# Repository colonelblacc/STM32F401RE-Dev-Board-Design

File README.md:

# STM32F401RETx — Custom PCB Design

> A compact, 2-layer custom PCB based on the **STM32F401RETx** microcontroller, featuring USB-C, SWD debugging, UART, SPI, I2C and GPIO expansion — designed in KiCad and fully verified with **0 DRC errors** and **0 ERC violations**.

---

## Board Preview

---

## Project Phases

This repository covers the complete design lifecycle:

| Phase   | Contents                                                                 | Status      |
|---------|--------------------------------------------------------------------------|-------------|
| Phase 1 | KiCad source files — schematic, PCB layout, project config               | ✅ Complete |
| Phase 2 | 3D renders, layer exports, BOM, DRC/ERC verification, design report      | ✅ Complete |

> **Phase 1** files (`STM32.kicad_sch`, `STM32.kicad_pcb`, `STM32.kicad_pro`) were uploaded in the first submission.
> **Phase 2** adds all supporting documentation, renders, and verification results — completing the full project.

---

## Repository Structure

```
STM32F401RE-Dev-Board-Design/
│
├── STM32.kicad_pcb                        # [Phase 1] KiCad PCB layout
├── STM32.kicad_pro                        # [Phase 1] KiCad project file
├── STM32.kicad_sch                        # [Phase 1] KiCad schematic
│
├── STM32_F401_Design_Report.pdf           # [Phase 2] Full design report
├── STM32_PDF.pdf                          # [Phase 2] Supplementary PDF
│
├── PCB Layout/
│   ├── STM32.zip                          # KiCad project archive
│   └── STM32_pcb_layer.zip                # Exported PCB layer files (Gerbers)
│
├── Render Images/
│   ├── STM32_img.png                      # 3D Render — Top View (clean)
│   ├── 3D Design.jpeg                     # 3D Render — KiCad Viewer Top
│   ├── IMAGE5.jpeg                        # 3D Render — PCB Back View
│   ├── IMAGE6.jpeg                        # 3D Render — Perspective View
│   ├── Layout Layer1.jpeg                 # F.Cu Front Copper Layer
│   ├── Layout Layer2.jpeg                 # B.Cu Back Copper Layer
│   ├── Schematic.jpeg                     # Full Schematic Diagram
│   ├── IMAGE1.jpeg                        # DRC Result — 0 Errors
│   └── IMAGE2.jpeg                        # ERC Result — 0 Violations
│
├── BOM/
│   ├── BOM.jpeg                           # Footprint Assignments View
│   └── BOM2.png                           # Bill of Materials Table
│
└── DRC ERC Results/
    ├── IMAGE1.jpeg     # DRC — 0 Violations
    └── IMAGE2.jpeg # ERC — 0 Violations
```

---

## Microcontroller

| Parameter       | Details                           |
|-----------------|-----------------------------------|
| **MCU**         | STM32F401RETx                     |
| **Package**     | LQFP-64 (10x10mm, 0.5mm pitch)    |
| **Core**        | ARM Cortex-M4 @ 84 MHz            |
| **Flash**       | 512 KB                            |
| **RAM**         | 96 KB SRAM                        |
| **EDA Tool**    | KiCad EDA 9.0.7                   |
| **PCB Layers**  | 2 (F.Cu + B.Cu)                   |

---

## Features & Connectivity

| Interface     | Connector/Ref | Description                           |
|---------------|---------------|---------------------------------------|
| **USB-C**     | J7            | USB 2.0 (USB_C_Receptacle_USB3.0_C6P)|
| **GPIO**      | J6            | 5-pin GPIO Expansion Header           |
| **SPI**       | J5            | VCC, SPI, GND Header                  |
| **UART**      | J3            | TX / RX Header                        |
| **I2C**       | J2 / J4       | SDA / SCL Header                      |
| **SWD**       | J2            | SWDIO, SWDCLK, IO, VCC, GND          |
| **RESET**     | SW1 + J4      | Tactile push button + Reset pin header|
| **Power**     | U1 (AMS1117)  | 3.3V LDO Regulator from USB 5V        |
| **Crystal**   | Y1            | 24 MHz SMD Crystal (3225-4Pin)        |
| **LED**       | D1            | Power / Status LED (0603)             |

---

## Schematic

The schematic is divided into functional blocks:

- **STM32F401** — Central MCU with all peripheral nets routed
- **Power Supply** — AMS1117-3.3 LDO with bulk and decoupling capacitors
- **USB-C Connector** — With 5.1k CC1/CC2 pull-down resistors (R7, R8)
- **Crystal** — 24 MHz with 22pF load capacitors C12, C13
- **Header Breakouts** — UART, SPI, I2C, GPIO, SWD
- **Mounting Holes** — H1–H4 (M2.5, 2.7mm diameter)

---

## PCB Layout

### Front Copper Layer — F.Cu

### Back Copper Layer — B.Cu

**PCB Statistics:**

| Parameter        | Value     |
|------------------|-----------|
| Pads             | 172       |
| Vias             | 44        |
| Track Segments   | 376       |
| Nets             | 65        |
| Unrouted         | **0**     |
| Track Width      | 0.25 mm   |

---

## Bill of Materials (BOM)

| Component              | Ref.    | Qty.   | Est. Unit Cost | Est. Total  |
|------------------------|---------|--------|----------------|-------------|
| STM32F401RETx MCU      | U2      | 1      | Rs. 350        | Rs. 350     |
| AMS1117-3.3 Regulator  | U1      | 1      | Rs. 15         | Rs. 15      |
| USB-C Connector        | J7      | 1      | Rs. 25         | Rs. 25      |
| Crystal 24 MHz         | Y1      | 1      | Rs. 10         | Rs. 10      |
| Ferrite Bead           | FB1     | 1      | Rs. 5          | Rs. 5       |
| Capacitors (0603/0805) | C1–C14  | 14     | Rs. 2          | Rs. 28      |
| Resistors (0603)       | R1–R8   | 8      | Rs. 2          | Rs. 16      |
| LED (0603)             | D1      | 1      | Rs. 3          | Rs. 3       |
| Reset Push Button      | SW1     | 1      | Rs. 5          | Rs. 5       |
| Pin Headers 2.54mm     | J2–J6   | 5 sets | Rs. 15         | Rs. 75      |
| Mounting Hardware M2.5 | H1–H4   | 4      | Rs. 3          | Rs. 12      |
| **Estimated Total**    |         |        |                | **Rs. 844** |

---

## DRC / ERC Verification

Both checks pass with **zero errors** — the design is fully clean.

### Design Rules Check (DRC) — 0 Violations

| Check              | Result |
|--------------------|--------|
| Violations         | **0**  |
| Unconnected Items  | **0**  |
| Schematic Parity   | **0**  |

### Electrical Rules Check (ERC) — 0 Violations

| Check    | Result |
|----------|--------|
| Errors   | **0**  |
| Warnings | **0**  |

---

## 3D Renders

<table align="center">
  <tr>
    <td align="center">
      <br/>
      <b>Top View — KiCad 3D Viewer</b>
    </td>
    <td align="center">
      <br/>
      <b>Bottom View</b>
    </td>
  </tr>
  <tr>
    <td align="center" colspan="2">
      <br/>
      <b>Perspective View</b>
    </td>
  </tr>
</table>

---

## KiCad Source Files (Phase 1)

The raw KiCad design files are at the root of this repository:

| File               | Description       |
|--------------------|-------------------|
| `STM32.kicad_pcb`  | PCB Layout        |
| `STM32.kicad_sch`  | Schematic         |
| `STM32.kicad_pro`  | KiCad Project     |

---

## Documents

| File                           | Description           |
|--------------------------------|-----------------------|
| `STM32_F401_Design_Report.pdf` | Full design report    |
| `STM32_PDF.pdf`                | Supplementary PDF     |
| `PCB Layout/STM32.zip`         | KiCad project archive |

---

## Tools Used

| Tool                | Version | Purpose                |
|---------------------|---------|------------------------|
| **KiCad EDA**       | 9.0.7   | Schematic + PCB Design |
| **KiCad 3D Viewer** | 9.0.7   | 3D Visualization       |

---

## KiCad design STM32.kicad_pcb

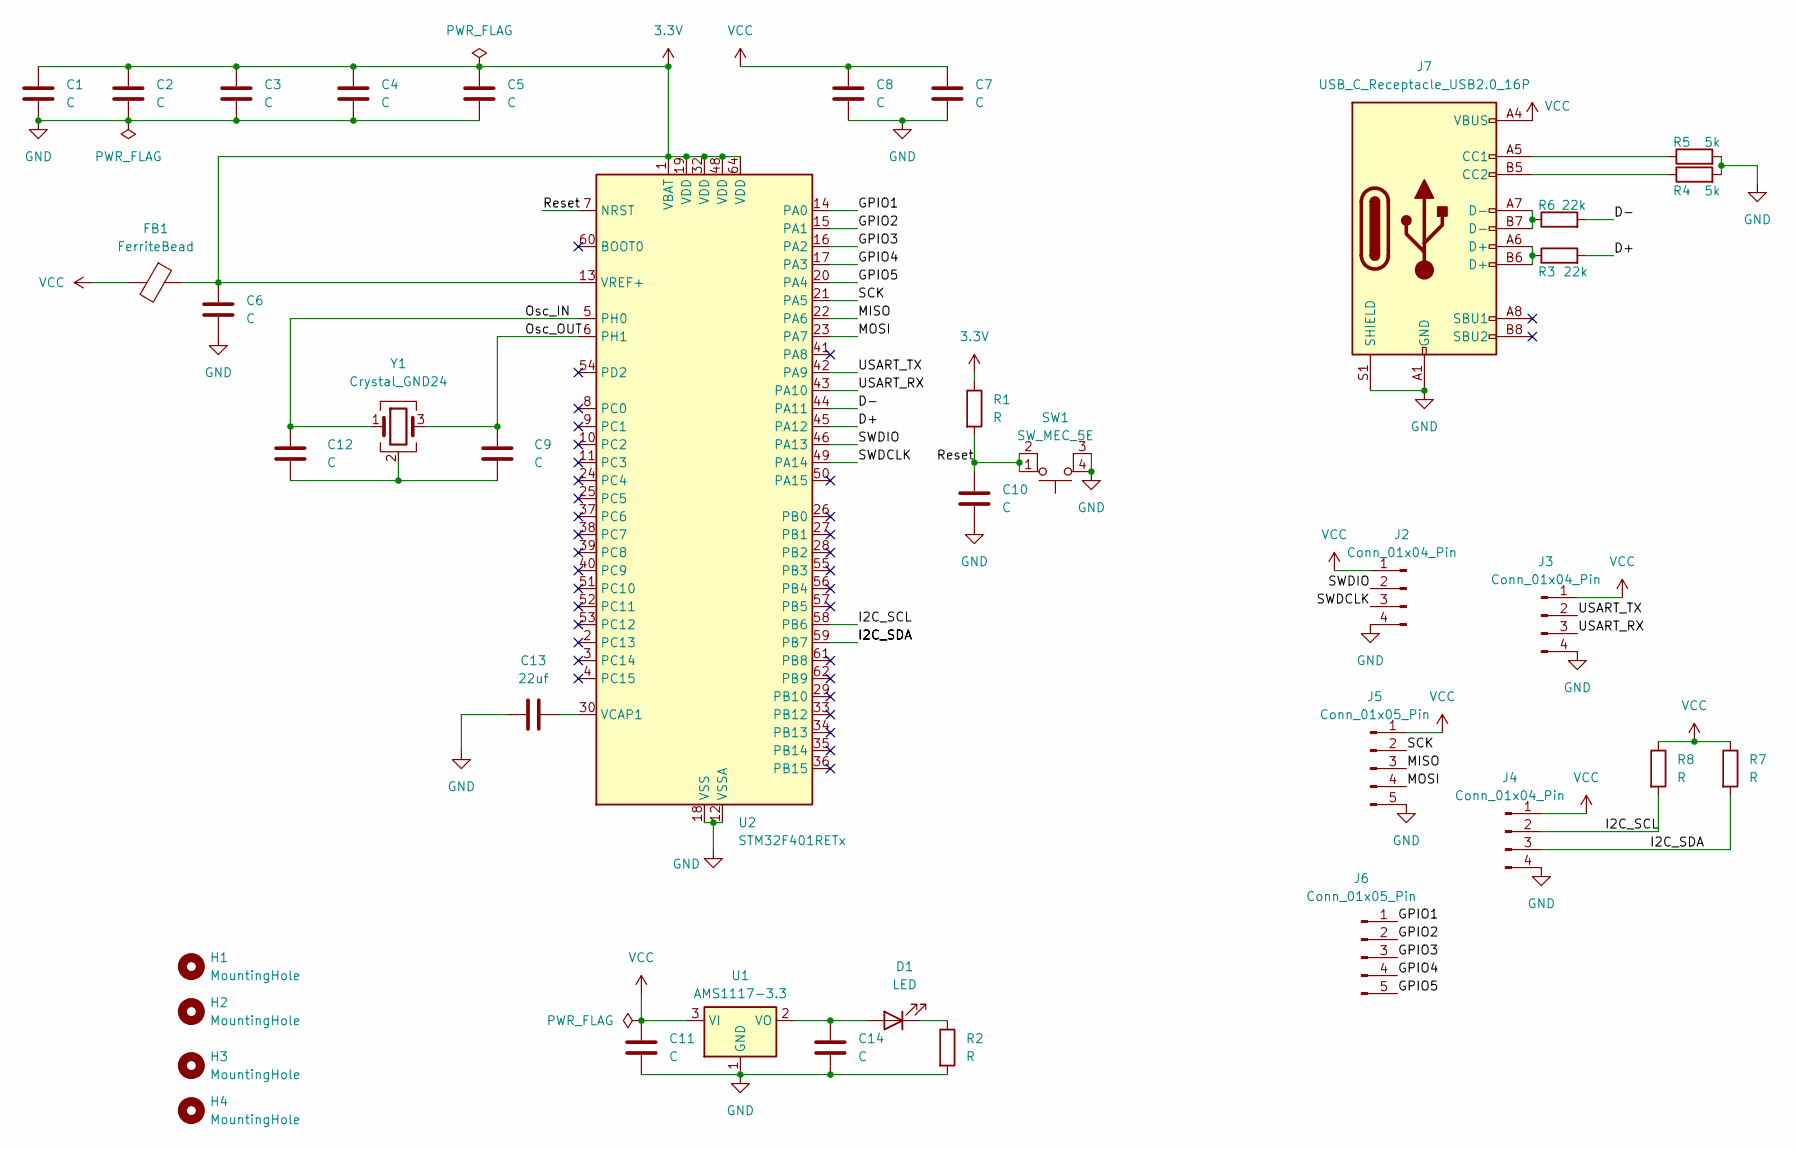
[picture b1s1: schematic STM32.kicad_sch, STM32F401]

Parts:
C1, C2, C3, C4, C5, C7, C8, C9, C10, C14: C; C_0603_1608Metric
C6, C11, C12: C; C_0805_2012Metric
C13: 22uf; C_0805_2012Metric
D1: LED; LED_0603_1608Metric
FB1: FerriteBead; L_0603_1608Metric
H1, H2, H3, H4: MountingHole; MountingHole_2.7mm_M2.5
J2, J3, J4: Conn_01x04_Pin; PinHeader_1x04_P2.54mm_Vertical
J5, J6: Conn_01x05_Pin; PinHeader_1x05_P2.54mm_Vertical
J7: USB_C_Receptacle_USB2.0_16P; USB_C_Receptacle_GCT_USB4105-xx-A_16P_TopMnt_Horizontal
R1, R2, R7, R8: R; R_0603_1608Metric
R3, R6: 22k; R_0603_1608Metric
R4, R5: 5k; R_0603_1608Metric
SW1: SW_MEC_5E; SW_Push_1P1T_NO_LED_E-Switch_TL1250
U1: AMS1117-3.3; SOT-223-3_TabPin2
U2: STM32F401RETx; LQFP-64_10x10mm_P0.5mm
Y1: Crystal_GND24; Crystal_SMD_3225-4Pin_3.2x2.5mm

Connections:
3.3V: C1.1, C2.1, C3.1, C4.1, C5.1, C6.1, FB1.1, R1.1, U2.1 (VBAT), U2.13 (VREF+), U2.19 (VDD), U2.32 (VDD), U2.48 (VDD), U2.64 (VDD)
/D+: R3.2, U2.45 (PA12)
/D-: R6.2, U2.44 (PA11)
/GPIO1: J6.1, U2.14 (PA0)
/GPIO2: J6.2, U2.15 (PA1)
/GPIO3: J6.3, U2.16 (PA2)
/GPIO4: J6.4, U2.17 (PA3)
/GPIO5: J6.5, U2.20 (PA4)
/I2C_SCL: J4.2, R8.2, U2.58 (PB6)
/I2C_SDA: J4.3, R7.2, U2.59 (PB7)
/MISO: J5.3, U2.22 (PA6)
/MOSI: J5.4, U2.23 (PA7)
/Osc_IN: C12.1, U2.5 (PH0), Y1.1
/Osc_OUT: C9.1, U2.6 (PH1), Y1.3
/Reset: C10.1, R1.2, SW1.1, SW1.2, U2.7 (NRST)
/SCK: J5.2, U2.21 (PA5)
/SWDCLK: J2.3, U2.49 (PA14)
/SWDIO: J2.2, U2.46 (PA13)
/USART_RX: J3.3, U2.43 (PA10)
/USART_TX: J3.2, U2.42 (PA9)
GND: C1.2, C2.2, C3.2, C4.2, C5.2, C6.2, C7.2, C8.2, C10.2, C11.2, C13.1, C14.2, J2.4, J3.4, J4.4, J5.5, J7.A1 (GND), J7.A12 (GND), J7.B1 (GND), J7.B12 (GND), J7.S1 (SHIELD), R2.2, R4.2, R5.2, SW1.3 (K), SW1.4 (A), U1.1 (GND), U2.12 (VSSA), U2.18 (VSS), U2.31 (VSS), U2.47 (VSS), U2.63 (VSS); also elsewhere on the board
unnamed: C9.2, C12.2, Y1.2 (G), Y1.4 (G)
unnamed: C14.1, D1.2 (A), U1.2 (VO)
unnamed: D1.1 (K), R2.1
unnamed: J7.A5 (CC1), R5.1
unnamed: J7.B5 (CC2), R4.1
unnamed: J7.A6 (D+), J7.B6 (D+), R3.1
unnamed: J7.A7 (D-), J7.B7 (D-), R6.1
unnamed: C13.2, U2.30 (VCAP1)
VCC: C7.1, C8.1, C11.1, FB1.2, J2.1, J3.1, J4.1, J5.1, J7.A4 (VBUS), J7.A9 (VBUS), J7.B4 (VBUS), J7.B9 (VBUS), R7.1, R8.1, U1.3 (VI); also elsewhere on the board

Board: 2 copper layers, 39 parts (0 on the bottom side), 32 nets, no tracks yet.

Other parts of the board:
J1: USB_C_Receptacle_USB2.0_14P; USB_C_Receptacle_HRO_TYPE-C-31-M-12

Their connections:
GND: J1.A1 (GND), J1.A12 (GND), J1.B1 (GND), J1.B12 (GND), J1.S1 (SHIELD); also elsewhere on the board
unnamed: J1.A6 (D+), J1.B6 (D+)
unnamed: J1.A7 (D-), J1.B7 (D-)
VCC: J1.A4 (VBUS), J1.A9 (VBUS), J1.B4 (VBUS), J1.B9 (VBUS); also elsewhere on the board
